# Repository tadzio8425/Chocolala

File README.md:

<div>
  <h1>  Chocolala  </h1>
</div>

### The IOT Chocolate Pot:

- Electronic instrumentation system for a reactor that prepares "hot" chocolate. Includes:
  - Continous weight and temperature measurement
  - Automatic liquid pouring
  - Controlled mixing speed
- Backend developed using the Arduino Framework and an ESP32 development board.
- Frontend mobile app developed using the Expo Framework and React-Native.
- Further documentation (in Spanish): [Documentación Chocolala](https://github.com/tadzio8425/Chocolala/files/12207769/Instrumentacion__Datasheet_Balanza.pdf)

- Developed in the *Universidad de Los Andes* for the class of *Instrumentación Electrónica (IELE-3206)*

## Developed by: 
<ul>
  <li>Juan Sebastián Ortega (https://github.com/tadzio8425)</li>
  <li>Nicolás Correal (https://github.com/Correaln47)</li>
  <li>Maria Alejandra Moreno (https://github.com/marialemor)</li>
  <li>Francisco Santamaría (f.santamaria@uniandes.edu.co)</li>
</ul>

## Frontend - App preview
| Index page | Main page |
| --- | --- |
|   ||

## Product Design

| Chain of used instrumentation |
| --- |
|   |

| PCB Design | PCB Prototype |
| --- | --- |
|||

| Prototype|
| --- |
|   |

## Demo

https://github.com/tadzio8425/Chocolala/assets/78126968/3fff56c4-ae32-456e-9e00-969c29b892ba

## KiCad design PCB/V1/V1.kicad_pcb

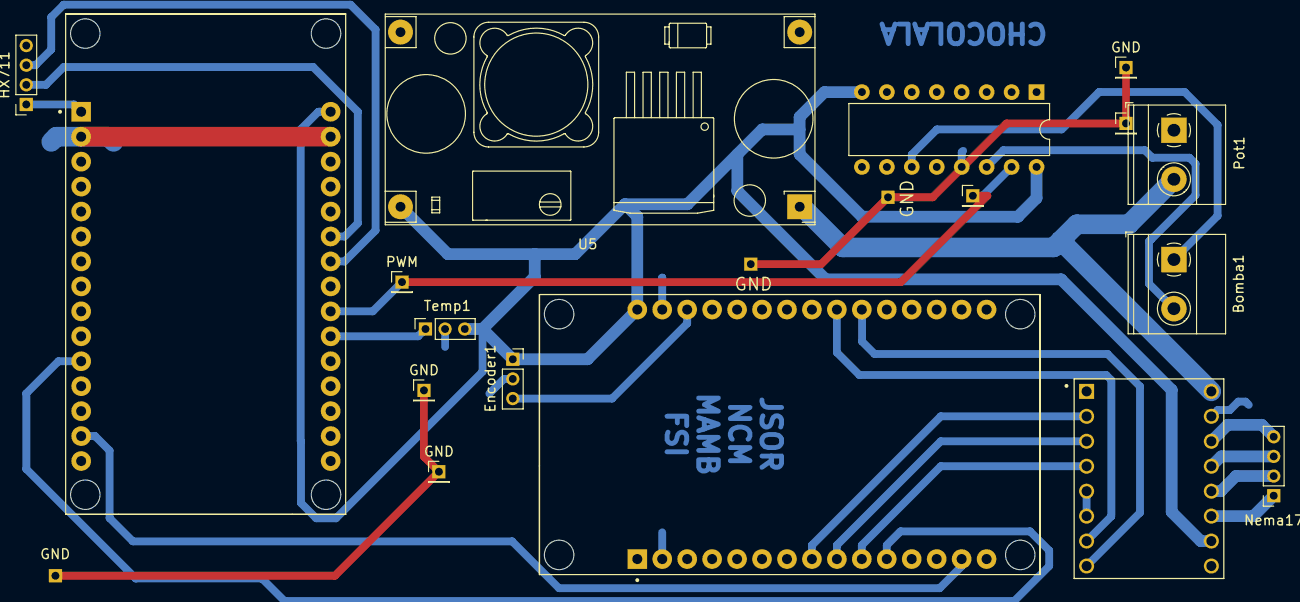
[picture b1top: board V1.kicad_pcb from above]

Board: 2 copper layers, 19 parts (0 on the bottom side), 23 nets.

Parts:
Bomba1: Screw_Terminal_01x02; TerminalBlock_Phoenix_MKDS-1,5-2_1x02_P5.00mm_Horizontal
Encoder1: Screw_Terminal_01x03; PinSocket_1x03_P2.00mm_Vertical
GND: (no value)
GND#2: (no value)
GND#3, GND#4, GND#5: Conn_01x01_Socket; PinHeader_1x01_P2.00mm_Vertical
HX711: Screw_Terminal_01x04; PinSocket_1x04_P2.00mm_Vertical
J3, J5: Conn_01x01_Socket; PinHeader_1x01_P2.00mm_Vertical
Nema17: Screw_Terminal_01x04; PinSocket_1x04_P2.00mm_Vertical
PWM: Conn_01x01_Socket; PinHeader_1x01_P2.00mm_Vertical
Pot1: Screw_Terminal_01x02; TerminalBlock_Phoenix_MKDS-1,5-2_1x02_P5.00mm_Horizontal
Temp1: Screw_Terminal_01x03; PinSocket_1x03_P2.00mm_Vertical
U1, U6: ESP32-DEVKIT-V1; MODULE_ESP32_DEVKIT_V1
U2: L293D; DIP-16_W7.62mm
U3: A4988; MODULE_A4988_STEPPER_MOTOR_DRIVER_CARRIER
U5: LM2596; YAAJ_DCDC_StepDown_LM2596

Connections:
3.3V: HX711.1, U1.1 (3V3)
12V: Pot1.2, U3.16 (VMOT), U5.1 (Vin)
+6V: Encoder1.1, Temp1.3, U1.30 (VIN), U2.8 (VCC2), U2.16 (VCC1), U3.10 (VDD), U5.4 (Vout), U6.30 (VIN)
DT: HX711.3, U1.24 (D26)
Dir: U3.8 (DIR), U6.21 (D32)
Encoder: Encoder1.3, U6.28 (D13)
GND: Encoder1.2, GND.1, GND#2.1, GND#3.1, GND#4.1, GND#5.1, HX711.4, J5.1, Pot1.1, Temp1.2, U1.2 (GND), U1.29 (GND), U2.10 (3A), U2.12 (GND), U2.13 (GND), U3.9 (GND), U3.15 (GND), U5.2 (GND), U5.3 (GND), U6.2 (GND), U6.29 (GND)
M1: U3.2 (MS1), U6.8 (D5)
M2: U3.3 (MS2), U6.9 (D18)
M3: U3.4 (MS3), U6.10 (D19)
Neg Bomba: Bomba1.1, U2.11 (3Y)
unnamed: Nema17.1, U3.11 (1B)
unnamed: Nema17.2, U3.12 (1A)
unnamed: Nema17.3, U3.13 (2A)
unnamed: Nema17.4, U3.14 (2B)
unnamed: U3.5 (~RESET), U3.6 (~SLEEP)
PWM Bomba: J3.1, PWM.1, U1.22 (D33), U2.15 (4A)
Pos Bomba: Bomba1.2, U2.14 (4Y)
SCK: HX711.2, U1.25 (D27)
SCL: U1.14 (D22), U6.14 (D22)
SDA: U1.11 (D21), U6.11 (D21)
Step: U3.7 (STEP), U6.22 (D33)
Temp: Temp1.1, U1.21 (D32)

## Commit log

2023-02-15 Hola Choco!
2023-02-18 Configuración base Balanza + Motobomba
2023-02-18 PID implementado
2023-02-18 Volumen agregado
2023-02-18 volumen
2023-02-18 casi todo arreglao
2023-02-18 Todo funcionando!
2023-02-19 touto
2023-02-20 PID semi
2023-02-22 Con segundo control
2023-02-24 yo no se
2023-02-24 Prueba Clase
2023-03-01 Prueba viernes 24
2023-03-03 Commit final motobomba
2023-03-03 Commit final
2023-03-03 Clase controlador creada e implementada
2023-03-03 Basura eliminada
2023-03-04 Vínculo API
2023-03-04 Wokwi
2023-03-04 funciona?
2023-03-04 más reciente
2023-03-05 melo caramelo
2023-03-05 GET general
2023-03-05 PUT referencia
2023-03-05 PUT waterFill
2023-03-05 Arreglao
2023-03-06 API funcionando!
2023-03-06 mensaje
2023-03-15 API FINAL
2023-03-17 Chocolalapp Expo creado
2023-03-18 Index page
2023-03-20 wowki wifi branch
2023-03-20 Conexion app-ESP exitosa!
2023-03-22 remake
2023-03-22 segunda pantalla
2023-03-26 tempy y peso
2023-03-27 dosificar
2023-03-27 optimizada :)
2023-03-27 mock actualizado
2023-03-28 calibrate on api
2023-03-28 Calibrar + boton stop
2023-03-28 ip setteable
2023-03-29 última versión
2023-03-29 inclusion motor
2023-03-29 arreglo pines
2023-03-29 modo test
2023-03-29 areglao
2023-04-05 mini cambios?
2023-04-13 Sangre, sudor y lagrimas
2023-04-13 prints caletos
2023-04-13 test
2023-04-13 crack
2023-04-14 antes de ventana recursiva
2023-04-14 DEBER'IA FUNCIONAR
2023-04-14 funciona
2023-04-15 zafo
2023-04-16 app responsive
2023-04-16 color arreglao
2023-04-16 testAPK
2023-04-17 arreglo reactive
2023-04-17 rpm slider agregao
2023-04-17 listones
2023-04-18 doble esp32
2023-04-18 arreglo
2023-04-18 cambio pin
2023-04-18 pines
2023-04-18 pines usables
2023-04-18 xdxd
2023-04-18 yonose
2023-04-18 UART
2023-04-18 bug fix
2023-04-18 prueba
2023-04-18 prueba string
2023-04-18 pruebita
2023-04-18 chatgpt
2023-04-18 arreglitos
2023-04-18 fixi
2023-04-18 cleanup
2023-04-18 Supa
2023-04-18 funciona al fin
2023-04-19 new funciona
2023-04-19 estrategias
2023-04-19 arreglo print
2023-04-19 a ver si si
2023-04-19 servirá?
2023-04-19 como debe funcionar
2023-04-19 todo listo
2023-04-19 se acabooooo
2023-04-19 supa fixed
2023-04-19 definitivo
2023-04-19 fin cali
2023-04-19 bugi
2023-04-19 se queda así
2023-04-19 control
2023-04-19 no maaa
2023-04-19 zthi
2023-04-19 fine tunning
2023-04-19 fine
2023-04-19 con tre
2023-04-19 ultra fine
2023-04-19 algo mal
2023-04-19 refix
2023-04-19 mini test
2023-04-19 post motor
2023-04-19 motor aguita
2023-04-19 C acabo la navidad
2023-04-19 mate el slider
2023-04-19 desired stop
2023-04-19 ENTREGA FINALIZADA
2023-04-19 Ojala
2023-04-19 nuevo pid
2023-04-21 cambios app slider
2023-04-25 pid finalizado
2023-04-26 timer calibración
2023-04-26 jiji
2023-04-26 request main 1
2023-04-26 Slave
2023-04-26 print
2023-04-26 cambiesitos
2023-04-26 doble cambios
2023-04-26 jackson
2023-04-26 realRPM agregado
2023-04-26 wiwiwi
2023-04-26 app changes
2023-04-26 limpieza
2023-04-26 libs
2023-04-26 cambios stepper a modulo
2023-04-26 mini error
2023-04-26 segundo mini error
2023-04-26 app bonita
2023-04-26 logo
2023-04-26 Create LICENCE
2023-05-03 pcb actualizada
2023-05-09 PCB implementada
2023-05-10 OneWire
2023-05-10 one wire arregladi
2023-05-10 temperatura codigo
2023-05-10 temperatura en back
2023-05-10 Funcionamiento Total Exitoso
2023-05-10 Cambio ícono
2023-05-10 auto ip
2023-05-10 arreglo icono gordo
